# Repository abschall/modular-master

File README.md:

# modular-master

_Eurorack & Modular projects from Abschall_

Welcome to the Abschall Modular Repository !

Explore my published Eurorack modules:

[**REP**](/REP) - A two-channel 1-in-3 Audio Buffered Multiple.

[**ATOM**](/ATOM) - A versatile three-channel ATtenuverter, Offset, and Mixer, available in sleek 6HP and expanded 10HP versions.

[**2xVCA**](/2xVCA) - A dual VCA, based on the Mutable Instrument's Veils 2 design. 

[**MOUNTS**](/MOUNTS) - A dual ADSR module, whose circuit is based upon the famous Roland SH-101 ADSR.

These utility modules were crafted with care, serving my personal needs and now shared with the community. Stay tuned for forthcoming much more creative modules currently in development.

<br/><br/>
If you have any questions or want to make any comments, feel free to contact me on [Mod Wiggler](https://modwiggler.com/) or by email abschall@hotmail.com.

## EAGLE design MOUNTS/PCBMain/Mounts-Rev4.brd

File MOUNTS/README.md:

# MOUNTS - Dual ADSR

<div align="justify">
  
MOUNTS is a dual ADSR module. Each enveloppe is based on the Roland SH-101 ADSR, with some added feature. 

_Status:_

March 2024: Added Mounts to proto-branch.  
Mounts: Revision 4 (03/2024) is missing the panel design, which is in creation. 
Revision 4 has not been tested yet and is still a prototype/ The circuit is an improvement upon the 2021 Rev3 version. 

</div>

_License:_  

This work is licensed under [CC BY-SA 4.0]. (https://creativecommons.org/licenses/by-sa/4.0/)

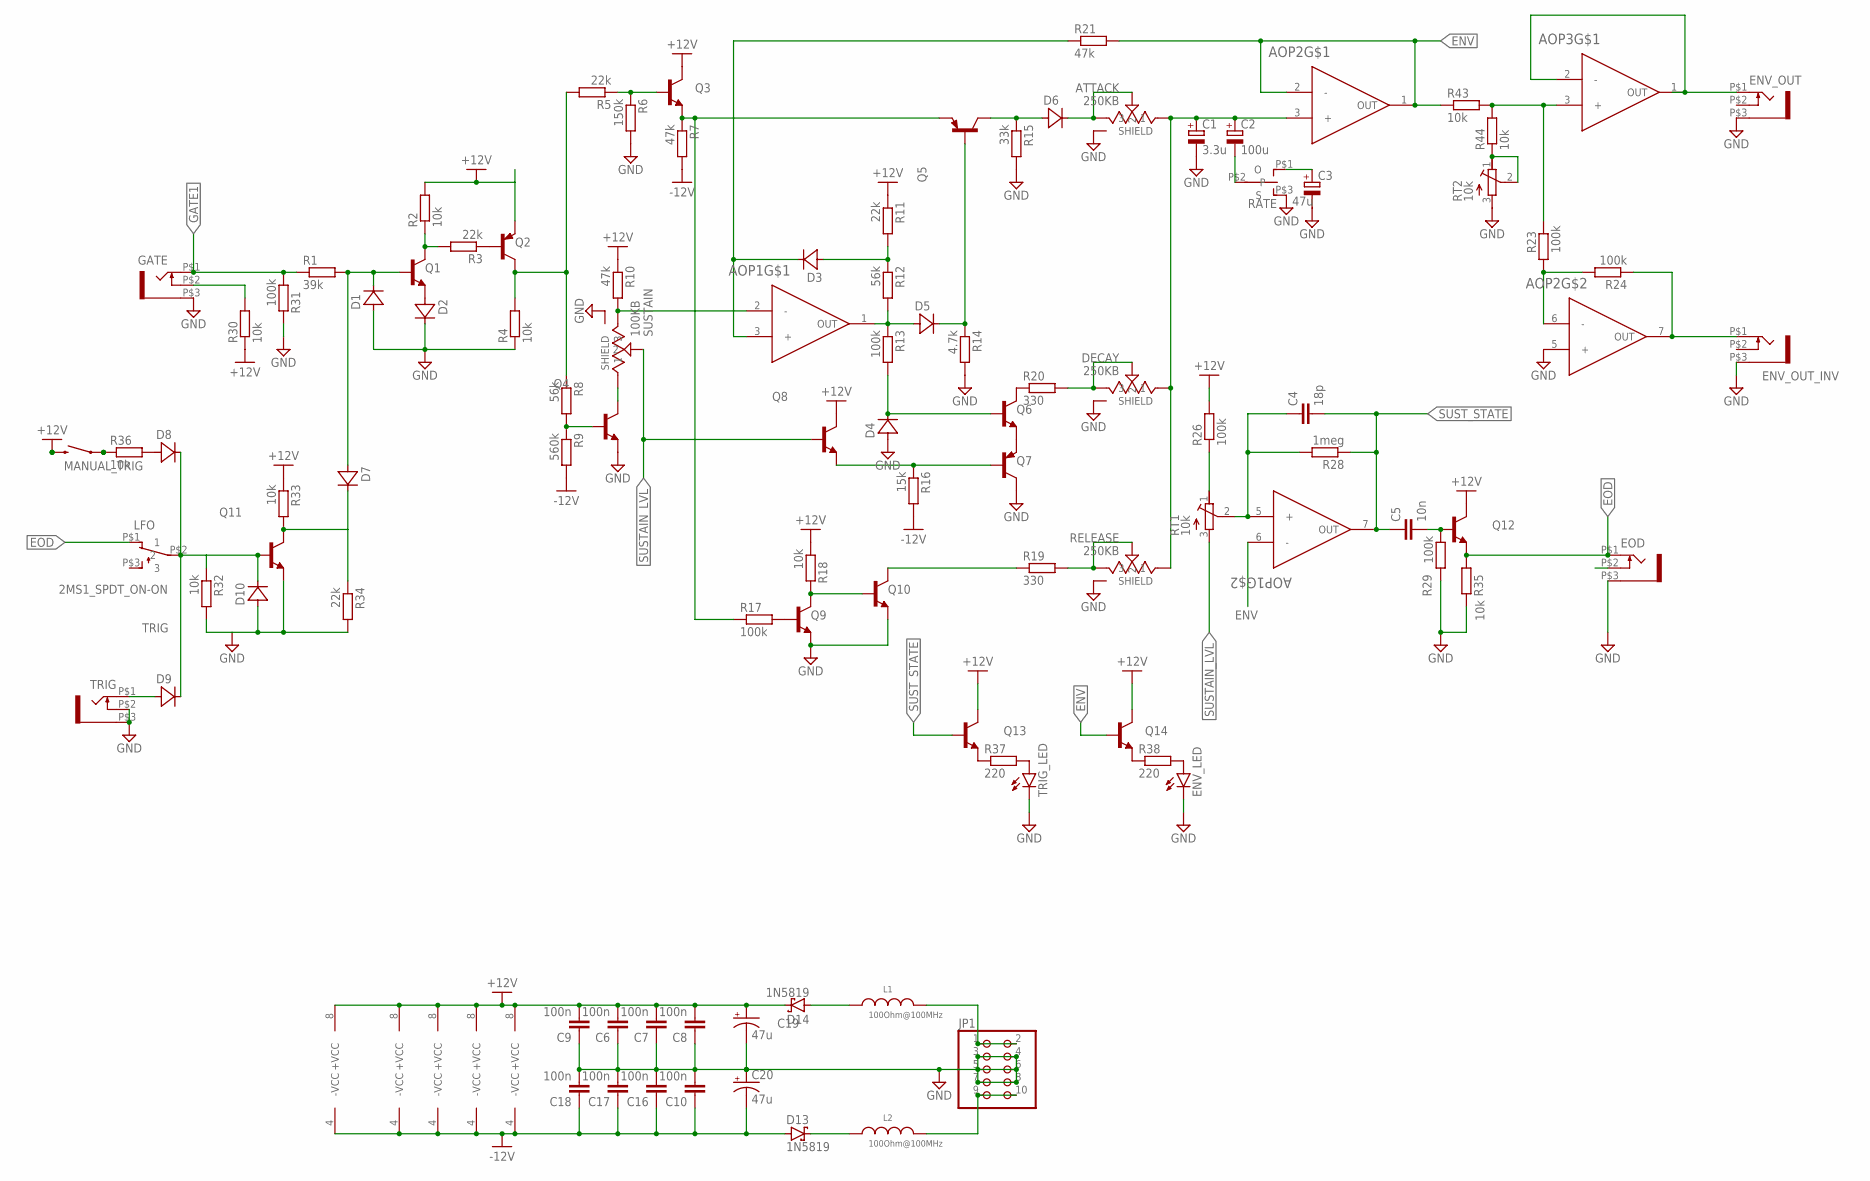
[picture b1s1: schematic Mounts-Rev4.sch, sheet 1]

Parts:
AOP1, AOP2, AOP3, AOP5, AOP6: TL072ACDR; SOIC8
ATTACK: 250KB; TRIM_PTA2043-2015CPB
C1: 3.3u; 153CLV-0405
C2: 100u; 153CLV-0605
C3: 47u; 153CLV-0605
C4: 18p; C0603
C5: 10n; C0603
C6, C7, C8, C9, C10, C16, C17, C18: 100n; C0603
C19, C20: 47u; PANASONIC_C
D1, D2, D3, D4, D5, D6, D7, D8, D9, D10: 1N4148WX; SOD323-W
D13, D14: 1N5819; SOD123
DECAY: 250KB; TRIM_PTA2043-2015CPB
ENV_LED: LED3MM
ENV_OUT: WQP-PJ301M-12_JACK
ENV_OUT_INV: WQP-PJ301M-12_JACK
EOD: WQP-PJ301M-12_JACK
GATE: WQP-PJ301M-12_JACK
JP1: PINHD-2X5; 2X05
L1, L2: 100Ohm@100MHz; WE-CBA_0603(W=2.2)
LFO: 2MS1_SPDT_ON-ON; 5FS1_SPDT
MANUAL_TRIG: MOMENTARY-SWITCH-SPST-PTH-6.0MM; TACTILE_SWITCH_PTH_6.0MM
Q1, Q3, Q4, Q6, Q8, Q9, Q10, Q11, Q12, Q13, Q14: MMBT3904; SOT23
Q2, Q5, Q7: MMBT3906; SOT23
R1: 39k; R0603
R2, R4, R18, R30, R32, R33, R35, R36, R43, R44: 10k; R0603
R3, R5, R11, R34: 22k; R0603
R6: 150k; R0603
R7, R10, R21: 47k; R0603
R8, R12: 56k; R0603
R9: 560k; R0603
R13, R17, R23, R24, R26, R29, R31: 100k; R0603
R14: 4.7k; R0603
R15: 33k; R0603
R16: 15k; R0603
R19, R20: 330; R0603
R28: 1meg; R0603
R37, R38: 220; R0603
RATE: 5FS1_SPDT_ON-OFF-ON; 5FS1_SPDT
RELEASE: 250KB; TRIM_PTA2043-2015CPB
RT1, RT2: 10k; RTRIM3314G
SUSTAIN: 100KB; TRIM_PTA2043-2015CPB
TRIG: WQP-PJ301M-12_JACK
TRIG_LED: LED3MM

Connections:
ENV: AOP1.6 (-), AOP2.1 (OUT), AOP2.2 (-), Q14.1 (B), R21.2, R43.1
EOD: EOD.P$1 (2), LFO.P$1 (1), Q12.2 (E), R35.1
GATE1: GATE.P$1 (2), R1.1, R31.1; also elsewhere on the board
GND: AOP2.5 (+), ATTACK.P1 (SHIELD), ATTACK.P2 (SHIELD), ATTACK.P3 (SHIELD), ATTACK.P4 (SHIELD), C1.-, C3.-, C6.1, C7.1, C8.1, C9.1, C10.2, C16.2, C17.2, C18.2, C19.-, C20.+, D1.A, D2.C, D4.A, D10.A, DECAY.P1 (SHIELD), DECAY.P2 (SHIELD), DECAY.P3 (SHIELD), DECAY.P4 (SHIELD), ENV_LED.K (C), ENV_OUT.P$3 (1), ENV_OUT_INV.P$3 (1), EOD.P$3 (1), GATE.P$3 (1), JP1.3, JP1.4, JP1.5, JP1.6, JP1.7, JP1.8, Q4.2 (E), Q7.3 (C), Q9.2 (E), Q10.2 (E), Q11.2 (E), R4.1, R6.2, R14.2, R15.2, R29.2, R31.2, R32.2, R34.2, R35.2, RATE.P$3 (S), RELEASE.P1 (SHIELD), RELEASE.P2 (SHIELD), RELEASE.P3 (SHIELD), RELEASE.P4 (SHIELD), RT2.3 (A), SUSTAIN.P1 (SHIELD), SUSTAIN.P2 (SHIELD), SUSTAIN.P3 (SHIELD), SUSTAIN.P4 (SHIELD), TRIG.P$2 (3), TRIG.P$3 (1), TRIG_LED.K (C); also elsewhere on the board
unnamed: D2.A, Q1.2 (E)
unnamed: D1.C, D7.A, Q1.1 (B), R1.2
unnamed: Q3.1 (B), R5.1, R6.1
unnamed: Q2.1 (B), R3.1
unnamed: JP1.1, JP1.2, L1.2
unnamed: Q1.3 (C), R2.1, R3.2
unnamed: AOP1.3 (+), D3.C, R21.1
unnamed: Q3.2 (E), Q5.2 (E), R7.1, R17.1
unnamed: Q4.1 (B), R8.2, R9.1
unnamed: AOP1.5 (+), C4.1, R28.2, RT1.2 (S)
unnamed: Q6.2 (E), Q7.2 (E)
unnamed: D3.A, R11.2, R12.1
unnamed: AOP1.1 (OUT), D5.A, R12.2, R13.1
unnamed: D4.C, Q6.1 (B), R13.2
unnamed: D5.C, Q5.1 (B), R14.1
unnamed: D6.A, Q5.3 (C), R15.1
unnamed: ATTACK.2, ATTACK.3, D6.C
unnamed: Q7.1 (B), Q8.2 (E), R16.1
unnamed: Q9.1 (B), R17.2
unnamed: AOP1.2 (-), R10.2, SUSTAIN.3
unnamed: Q9.3 (C), Q10.1 (B), R18.2
unnamed: Q10.3 (C), R19.1
unnamed: Q6.3 (C), R20.1
unnamed: DECAY.2, DECAY.3, R20.2
unnamed: R19.2, RELEASE.2, RELEASE.3
unnamed: AOP2.3 (+), ATTACK.1, C1.+, C2.+, DECAY.1, RELEASE.1
unnamed: Q4.3 (C), SUSTAIN.1
unnamed: AOP2.6 (-), R23.1, R24.2
unnamed: AOP3.1 (OUT), AOP3.2 (-), ENV_OUT.P$1 (2)
unnamed: GATE.P$2 (3), R30.2
unnamed: Q2.3 (C), R4.2, R5.2, R8.1
unnamed: R26.1, RT1.1 (E)
unnamed: D8.A, R36.2
unnamed: R44.1, RT2.1 (E), RT2.2 (S)
unnamed: D9.A, TRIG.P$1 (2)
unnamed: D7.C, Q11.3 (C), R33.2, R34.1
unnamed: C5.2, Q12.1 (B), R29.1
unnamed: MANUAL_TRIG.3 (2), R36.1
unnamed: C2.-, RATE.P$2
unnamed: C3.+, RATE.P$1 (O)
unnamed: Q13.2 (E), R37.1
unnamed: R37.2, TRIG_LED.A
unnamed: Q14.2 (E), R38.1
unnamed: ENV_LED.A, R38.2
unnamed: AOP2.7 (OUT), ENV_OUT_INV.P$1 (2), R24.1
unnamed: AOP3.3 (+), R23.2, R43.2, R44.2
unnamed: JP1.9, JP1.10, L2.2
unnamed: D14.A, L1.1
unnamed: D13.C, L2.1
SUSTAIN_LVL: Q8.1 (B), RT1.3 (A), SUSTAIN.2
SUST_STATE: AOP1.7 (OUT), C4.2, C5.1, Q13.1 (B), R28.1
TRIG: D8.C, D9.C, D10.C, LFO.P$2 (2), Q11.1 (B), R32.1
VCC: AOP1.8 (+VCC), AOP2.8 (+VCC), AOP3.8 (+VCC), AOP5.8 (+VCC), AOP6.8 (+VCC), C6.2, C7.2, C8.2, C9.2, C19.+, D14.C, MANUAL_TRIG.1, Q2.2 (E), Q3.3 (C), Q8.3 (C), Q12.3 (C), Q13.3 (C), Q14.3 (C), R2.2, R10.1, R11.1, R18.1, R26.2, R30.1, R33.1; also elsewhere on the board
VDD: AOP1.4 (-VCC), AOP2.4 (-VCC), AOP3.4 (-VCC), AOP5.4 (-VCC), AOP6.4 (-VCC), C10.1, C16.1, C17.1, C18.1, C20.-, D13.A, R7.2, R9.2, R16.2; also elsewhere on the board

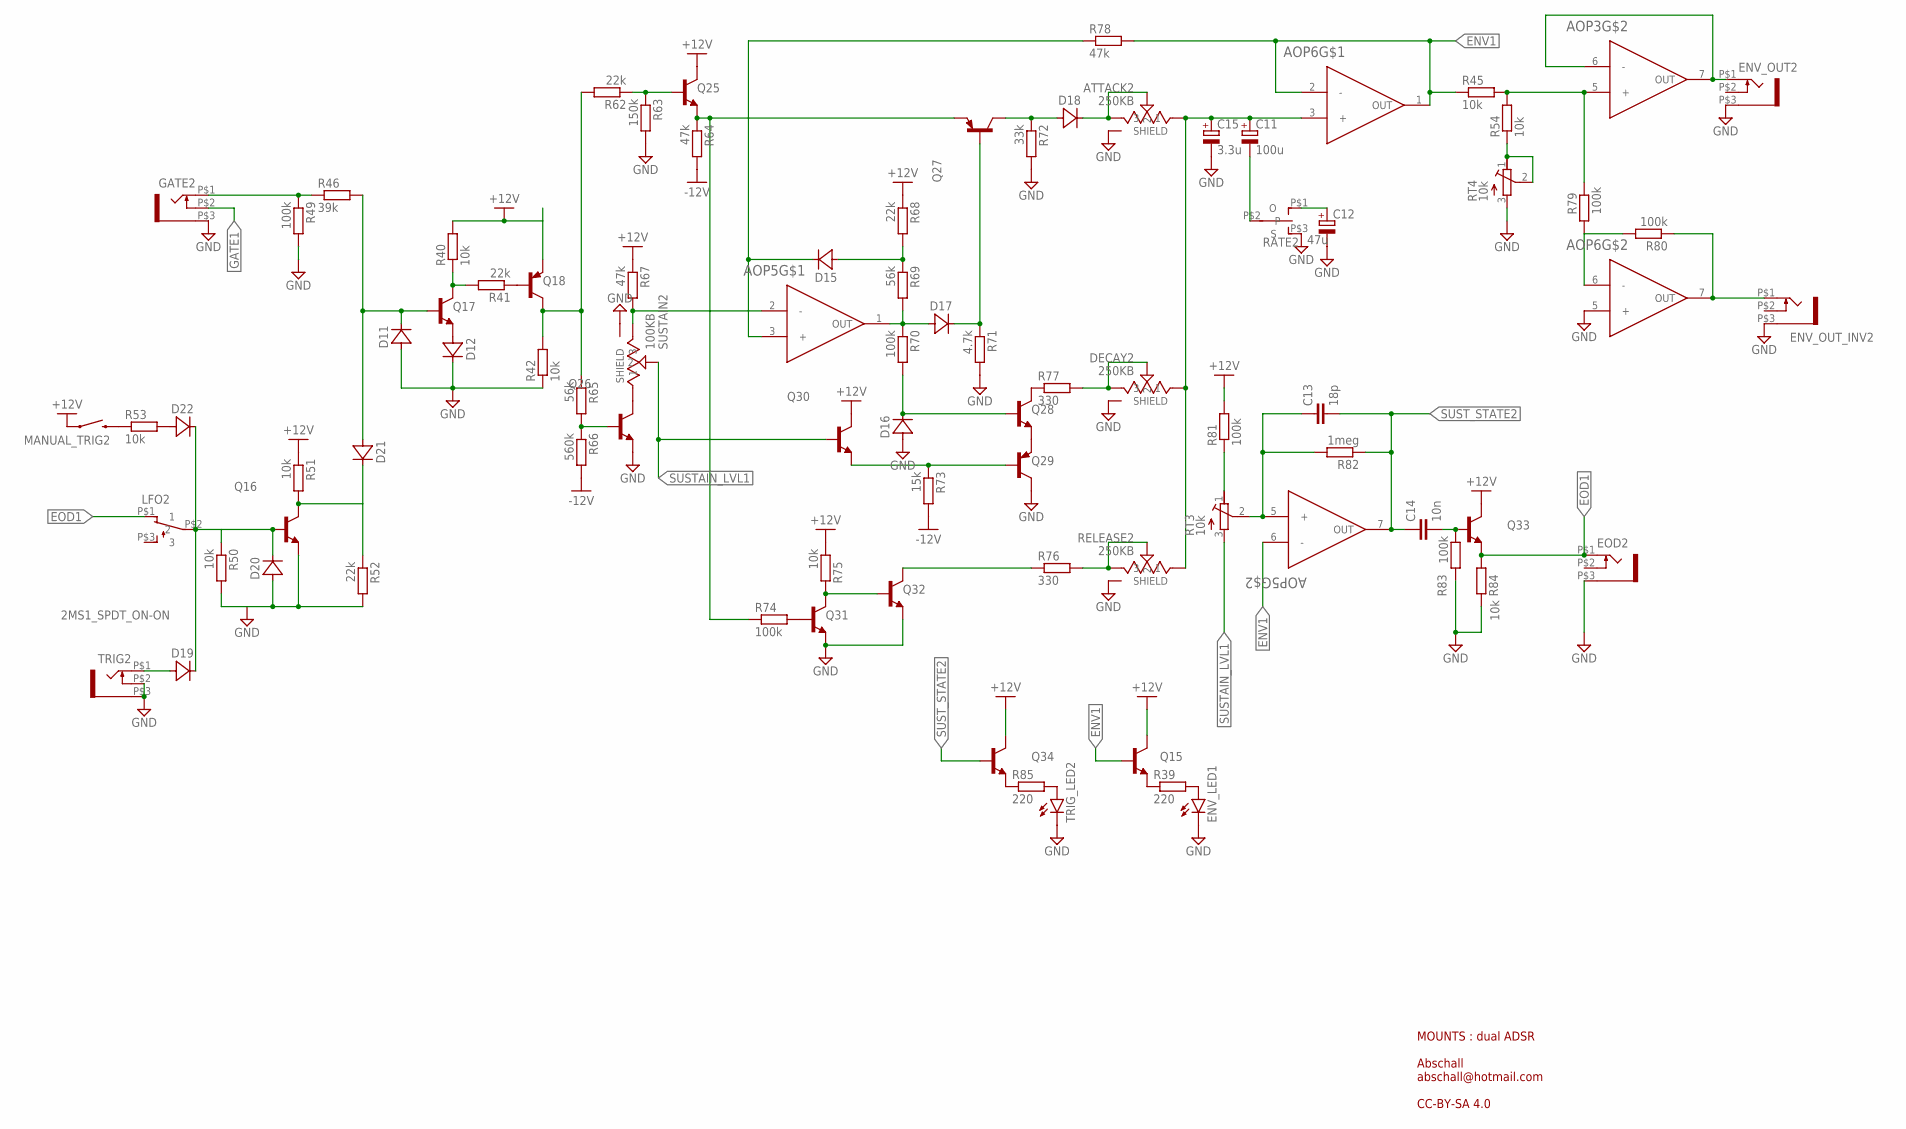
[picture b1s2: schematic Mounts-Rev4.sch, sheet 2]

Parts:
AOP3, AOP5, AOP6: TL072ACDR; SOIC8
ATTACK2: 250KB; TRIM_PTA2043-2015CPB
C11: 100u; 153CLV-0605
C12: 47u; 153CLV-0605
C13: 18p; C0603
C14: 10n; C0603
C15: 3.3u; 153CLV-0405
D11, D12, D15, D16, D17, D18, D19, D20, D21, D22: 1N4148WX; SOD323-W
DECAY2: 250KB; TRIM_PTA2043-2015CPB
ENV_LED1: LED3MM
ENV_OUT2: WQP-PJ301M-12_JACK
ENV_OUT_INV2: WQP-PJ301M-12_JACK
EOD2: WQP-PJ301M-12_JACK
GATE2: WQP-PJ301M-12_JACK
LFO2: 2MS1_SPDT_ON-ON; 5FS1_SPDT
MANUAL_TRIG2: MOMENTARY-SWITCH-SPST-PTH-6.0MM; TACTILE_SWITCH_PTH_6.0MM
Q15, Q16, Q17, Q25, Q26, Q28, Q30, Q31, Q32, Q33, Q34: MMBT3904; SOT23
Q18, Q27, Q29: MMBT3906; SOT23
R39, R85: 220; R0603
R40, R42, R45, R50, R51, R53, R54, R75, R84: 10k; R0603
R41, R52, R62, R68: 22k; R0603
R46: 39k; R0603
R49, R70, R74, R79, R80, R81, R83: 100k; R0603
R63: 150k; R0603
R64, R67, R78: 47k; R0603
R65, R69: 56k; R0603
R66: 560k; R0603
R71: 4.7k; R0603
R72: 33k; R0603
R73: 15k; R0603
R76, R77: 330; R0603
R82: 1meg; R0603
RATE2: 5FS1_SPDT_ON-OFF-ON; 5FS1_SPDT
RELEASE2: 250KB; TRIM_PTA2043-2015CPB
RT3, RT4: 10k; RTRIM3314G
SUSTAIN2: 100KB; TRIM_PTA2043-2015CPB
TRIG2: WQP-PJ301M-12_JACK
TRIG_LED2: LED3MM

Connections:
ENV1: AOP5.6 (-), AOP6.1 (OUT), AOP6.2 (-), Q15.1 (B), R45.1, R78.2
EOD1: EOD2.P$1 (2), LFO2.P$1 (1), Q33.2 (E), R84.1
GATE1: GATE2.P$2 (3); also elsewhere on the board
GND: AOP6.5 (+), ATTACK2.P1 (SHIELD), ATTACK2.P2 (SHIELD), ATTACK2.P3 (SHIELD), ATTACK2.P4 (SHIELD), C12.-, C15.-, D11.A, D12.C, D16.A, D20.A, DECAY2.P1 (SHIELD), DECAY2.P2 (SHIELD), DECAY2.P3 (SHIELD), DECAY2.P4 (SHIELD), ENV_LED1.K (C), ENV_OUT2.P$3 (1), ENV_OUT_INV2.P$3 (1), EOD2.P$3 (1), GATE2.P$3 (1), Q16.2 (E), Q26.2 (E), Q29.3 (C), Q31.2 (E), Q32.2 (E), R42.1, R49.2, R50.2, R52.2, R63.2, R71.2, R72.2, R83.2, R84.2, RATE2.P$3 (S), RELEASE2.P1 (SHIELD), RELEASE2.P2 (SHIELD), RELEASE2.P3 (SHIELD), RELEASE2.P4 (SHIELD), RT4.3 (A), SUSTAIN2.P1 (SHIELD), SUSTAIN2.P2 (SHIELD), SUSTAIN2.P3 (SHIELD), SUSTAIN2.P4 (SHIELD), TRIG2.P$2 (3), TRIG2.P$3 (1), TRIG_LED2.K (C); also elsewhere on the board
unnamed: AOP6.6 (-), R79.1, R80.2
unnamed: AOP3.5 (+), R45.2, R54.2, R79.2
unnamed: D12.A, Q17.2 (E)
unnamed: Q15.2 (E), R39.1
unnamed: ENV_LED1.A, R39.2
unnamed: D11.C, D21.A, Q17.1 (B), R46.2
unnamed: Q18.1 (B), R41.1
unnamed: Q17.3 (C), R40.1, R41.2
unnamed: Q18.3 (C), R42.2, R62.2, R65.1
unnamed: GATE2.P$1 (2), R46.1, R49.1
unnamed: R54.1, RT4.1 (E), RT4.2 (S)
unnamed: D21.C, Q16.3 (C), R51.2, R52.1
unnamed: D19.A, TRIG2.P$1 (2)
unnamed: D22.A, R53.2
unnamed: MANUAL_TRIG2.3 (2), R53.1
unnamed: AOP3.6 (-), AOP3.7 (OUT), ENV_OUT2.P$1 (2)
unnamed: AOP5.2 (-), R67.2, SUSTAIN2.3
unnamed: Q26.3 (C), SUSTAIN2.1
unnamed: Q25.1 (B), R62.1, R63.1
unnamed: Q25.2 (E), Q27.2 (E), R64.1, R74.1
unnamed: Q26.1 (B), R65.2, R66.1
unnamed: AOP5.3 (+), D15.C, R78.1
unnamed: D15.A, R68.2, R69.1
unnamed: AOP5.1 (OUT), D17.A, R69.2, R70.1
unnamed: D16.C, Q28.1 (B), R70.2
unnamed: D17.C, Q27.1 (B), R71.1
unnamed: D18.A, Q27.3 (C), R72.1
unnamed: ATTACK2.2, ATTACK2.3, D18.C
unnamed: Q28.2 (E), Q29.2 (E)
unnamed: Q29.1 (B), Q30.2 (E), R73.1
unnamed: Q31.1 (B), R74.2
unnamed: Q31.3 (C), Q32.1 (B), R75.2
unnamed: Q32.3 (C), R76.1
unnamed: Q28.3 (C), R77.1
unnamed: DECAY2.2, DECAY2.3, R77.2
unnamed: R76.2, RELEASE2.2, RELEASE2.3
unnamed: AOP6.3 (+), ATTACK2.1, C11.+, C15.+, DECAY2.1, RELEASE2.1
unnamed: AOP6.7 (OUT), ENV_OUT_INV2.P$1 (2), R80.1
unnamed: R81.1, RT3.1 (E)
unnamed: AOP5.5 (+), C13.1, R82.2, RT3.2 (S)
unnamed: C14.2, Q33.1 (B), R83.1
unnamed: C11.-, RATE2.P$2
unnamed: C12.+, RATE2.P$1 (O)
unnamed: Q34.2 (E), R85.1
unnamed: R85.2, TRIG_LED2.A
SUSTAIN_LVL1: Q30.1 (B), RT3.3 (A), SUSTAIN2.2
SUST_STATE2: AOP5.7 (OUT), C13.2, C14.1, Q34.1 (B), R82.1
TRIG1: D19.C, D20.C, D22.C, LFO2.P$2 (2), Q16.1 (B), R50.1
VCC: MANUAL_TRIG2.1, Q15.3 (C), Q18.2 (E), Q25.3 (C), Q30.3 (C), Q33.3 (C), Q34.3 (C), R40.2, R51.1, R67.1, R68.1, R75.1, R81.2; also elsewhere on the board
VDD: R64.2, R66.2, R73.2; also elsewhere on the board

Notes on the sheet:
MOUNTS : dual ADSR Abschall abschall@hotmail.com CC-BY-SA 4.0

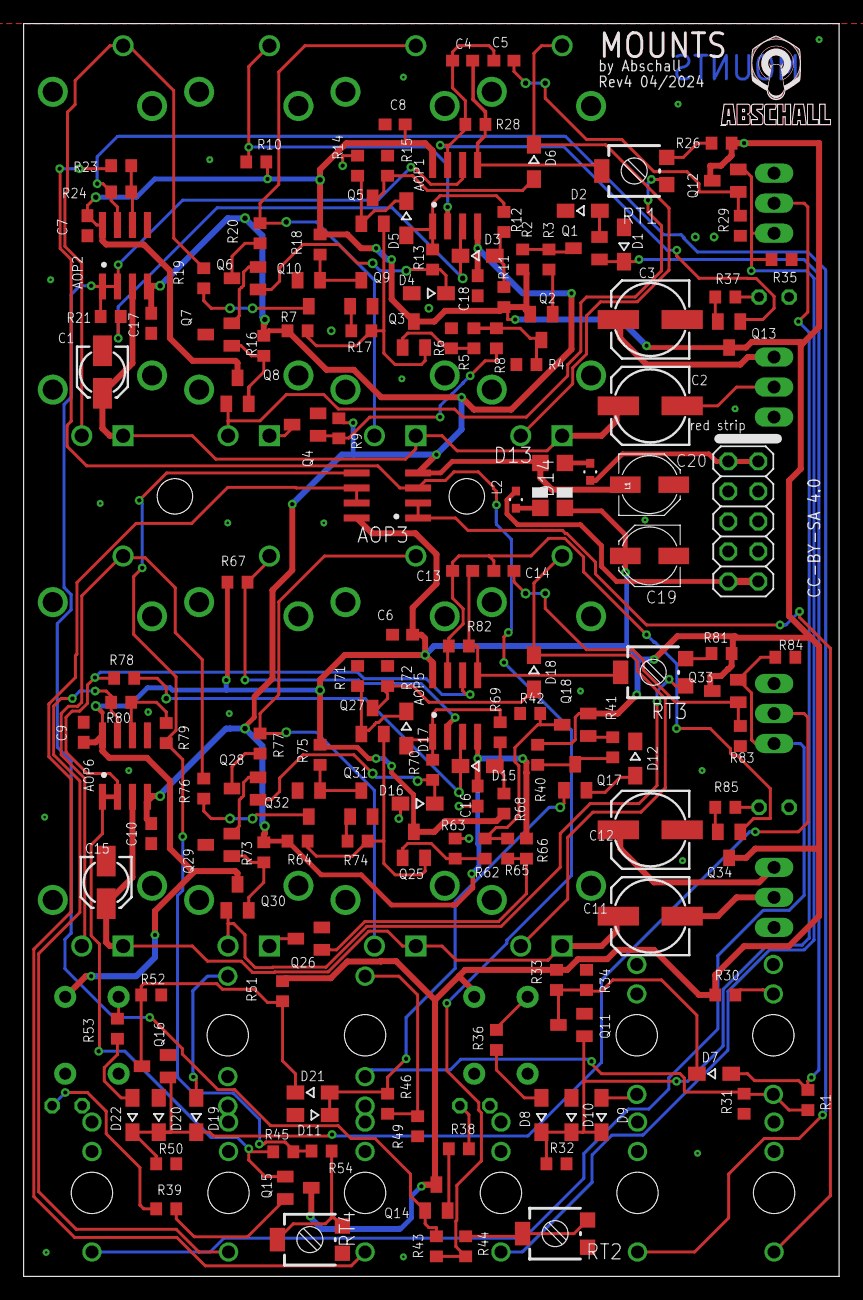
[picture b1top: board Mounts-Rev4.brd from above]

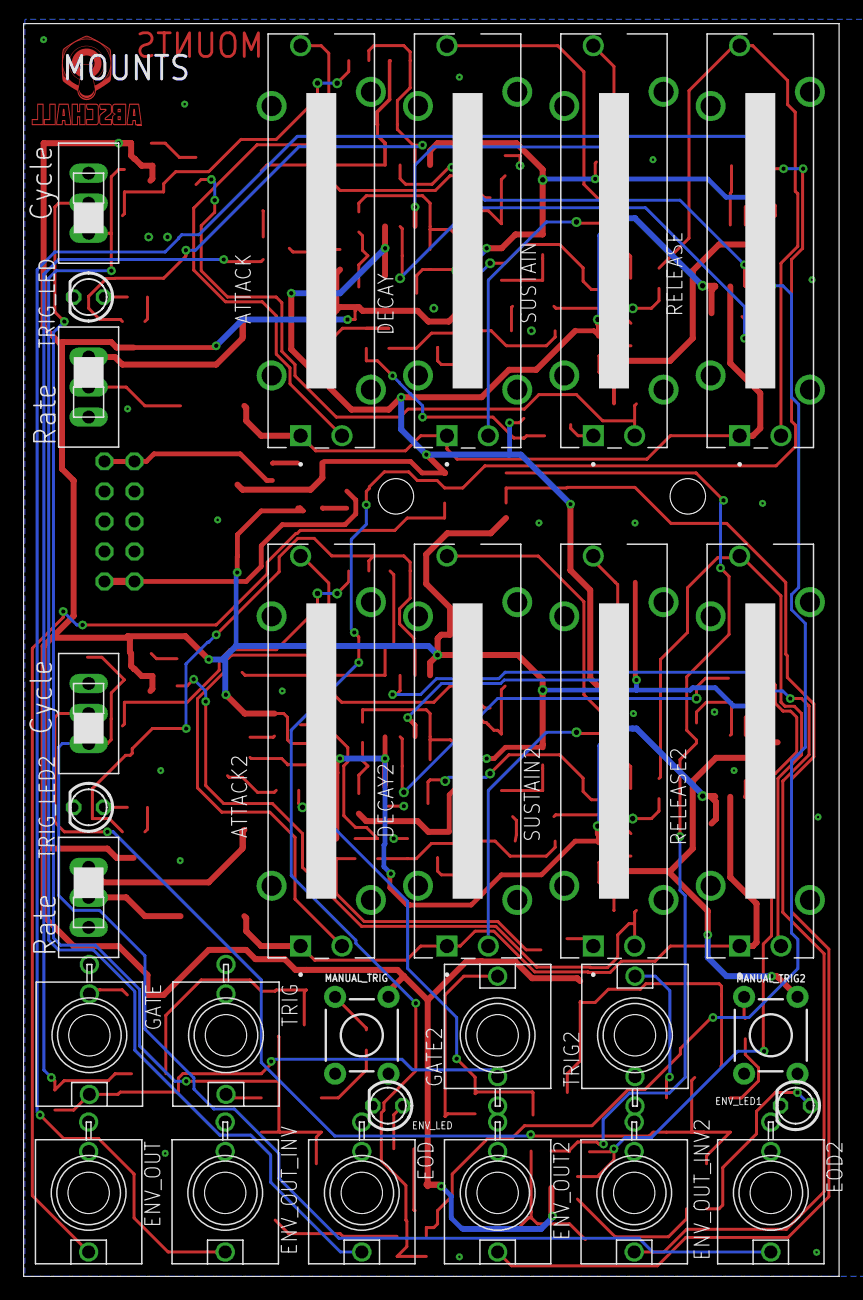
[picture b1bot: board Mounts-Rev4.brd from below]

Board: 2 copper layers, 69.0 x 106.0 mm, 183 parts (28 on the bottom side), 108 nets.

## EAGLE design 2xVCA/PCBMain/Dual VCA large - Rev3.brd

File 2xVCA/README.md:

# 2x VCA - Dual Voltage-Controlled Amplifier

<div align="justify">
  
2x VCA is a two-channel VCA based on Mutable Instruments' Veils, designed by Émilie Gillet. It features two separate voltage-controlled amplifiers, each with gain and response curve potentiometers, which are variable from linear to exponential. The PCB has been adapted to create a larger, more performance-friendly module for my purposes, providing more space between the jacks and knobs.

The module is 8HP wide and 21mm deep.

The PCB utilizes 0805 format surface-mount device (SMD) components.

</div>

_Status:_

March 2024: Publication of the project.  
2xVCA: Revision 3 (03/2022)  

_License:_  

This work is licensed under [CC BY-SA 3.0]. Circuit by Émilie GILLET, adaptation by Abschall. (https://creativecommons.org/licenses/by-sa/3.0/)

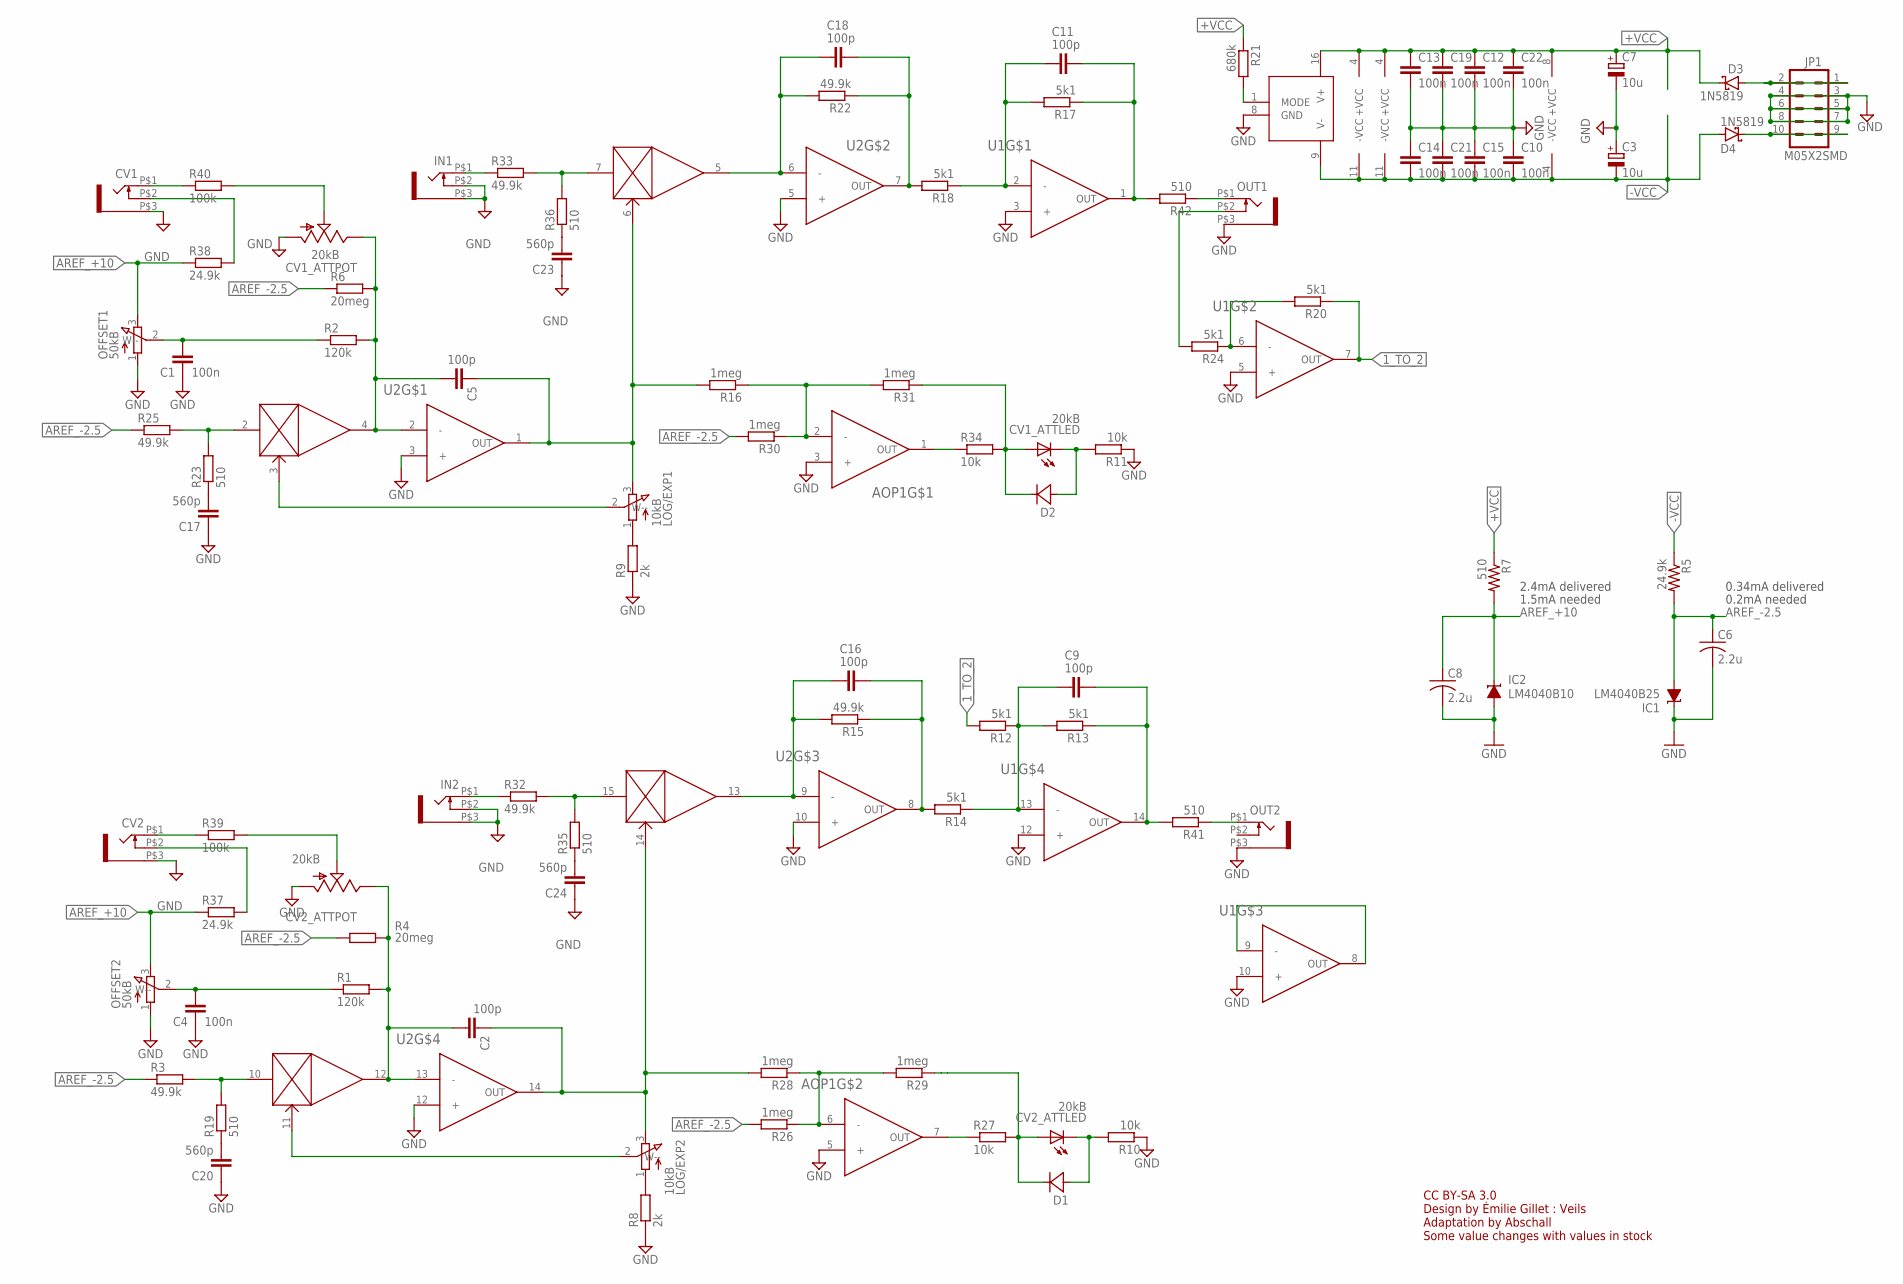
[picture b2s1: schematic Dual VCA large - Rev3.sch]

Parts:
AOP1: TL072ACDR; SOIC8
C1, C4, C10, C12, C13, C14, C15, C19, C21, C22: 100n; C0805K
C2, C5, C9, C11, C16, C18: 100p; C0805K
C3, C7: 10u; PANASONIC_B
C6, C8: 2.2u; C0805
C17, C20, C23, C24: 560p; C0805K
CV1, CV2: WQP-PJ301M-12_JACK
CV1_ATT, CV2_ATT: 20kB; BOURNS_SLIDER
D1, D2: 1N4148WX; SOD323-W
D3, D4: 1N5819; SOD123
IC1: LM4040B25; DBZ_R-PDSO-G3
IC2: LM4040B10; DBZ_R-PDSO-G3
IN1, IN2: WQP-PJ301M-12_JACK
JP1: M05X2SMD; 2X5-SMD
LOG/EXP1, LOG/EXP2: 10kB; ALPHA9MM-SH
OFFSET1, OFFSET2: 50kB; ALPHA9MM-SH
OUT1, OUT2: WQP-PJ301M-12_JACK
R1, R2: 120k; R0805
R3, R15, R22, R25, R32, R33: 49.9k; R0805
R4, R6: 20meg; R0805
R5, R37, R38: 24.9k; R0805
R7, R19, R23, R35, R36, R41, R42: 510; R0805
R8, R9: 2k; R0805
R10, R11, R27, R34: 10k; R0805
R12, R13, R14, R17, R18, R20, R24: 5k1; R0805
R16, R26, R28, R29, R30, R31: 1meg; R0805
R21: 680k; R0805
R39, R40: 100k; R0805
U1, U2: TL74CD; SO14
VCA1: V2164SOIC16N; SOIC16N

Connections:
1_TO_2: R12.2, R20.1, U1.7 (OUT)
+VCC: AOP1.8 (+VCC), C7.+, C12.1, C13.1, C19.1, C22.1, D3.C, R7.1, R21.1, U1.4 (+VCC), U2.4 (+VCC), VCA1.16 (V+)
-VCC: AOP1.4 (-VCC), C3.-, C10.2, C14.2, C15.2, C21.2, D4.A, R5.1, U1.11 (-VCC), U2.11 (-VCC), VCA1.9 (V-)
AREF_+10: C8.1, IC2.1 (C), OFFSET1.3, OFFSET2.3, R7.2, R37.1, R38.1
AREF_-2.5: C6.1, IC1.2 (A), R3.1, R4.1, R5.2, R6.1, R25.1, R26.2, R30.2
GND: AOP1.3 (+), AOP1.5 (+), C1.1, C3.+, C4.1, C6.2, C7.-, C8.2, C10.1, C12.2, C13.2, C14.1, C15.1, C17.1, C19.2, C20.1, C21.1, C22.2, C23.1, C24.1, CV1.P$3 (1), CV1_ATT.1 (A), CV2.P$3 (1), CV2_ATT.1 (A), IC1.1 (C), IC2.2 (A), IN1.P$2 (3), IN1.P$3 (1), IN2.P$2 (3), IN2.P$3 (1), JP1.3, JP1.4, JP1.5, JP1.6, JP1.7, JP1.8, OFFSET1.1, OFFSET2.1, OUT1.P$3 (1), OUT2.P$3 (1), R8.1, R9.1, R10.1, R11.1, U1.3 (+), U1.5 (+), U1.10 (+), U1.12 (+), U2.3 (+), U2.5 (+), U2.10 (+), U2.12 (+), VCA1.8 (GND)
unnamed: C23.2, R36.1
unnamed: CV2.P$1 (2), R39.1
unnamed: R33.2, R36.2, VCA1.7 (IN)
unnamed: C18.2, R22.2, U2.6 (-), VCA1.5 (OUT)
unnamed: C5.2, CV1_ATT.3 (E), R2.2, R6.2, U2.2 (-), VCA1.4 (OUT)
unnamed: IN2.P$1 (2), R32.1
unnamed: R21.2, VCA1.1 (MODE)
unnamed: C1.2, OFFSET1.2 (W--), R2.1
unnamed: C5.1, LOG/EXP1.3, R16.2, U2.1 (OUT), VCA1.6 (CV)
unnamed: C17.2, R23.1
unnamed: LOG/EXP1.1, R9.2
unnamed: R23.2, R25.2, VCA1.2 (IN)
unnamed: LOG/EXP1.2 (W--), VCA1.3 (CV)
unnamed: CV1_ATT.2 (S), R40.2
unnamed: C11.2, R17.2, R18.1, U1.2 (-)
unnamed: R20.2, R24.1, U1.6 (-)
unnamed: CV1_ATT.E (C), D2.A, R11.2
unnamed: CV2_ATT.B (A), D1.C, R27.2, R29.1
unnamed: IN1.P$1 (2), R33.1
unnamed: CV1.P$2 (3), R38.2
unnamed: OUT1.P$1 (2), R42.1
unnamed: OUT1.P$2 (3), R24.2
unnamed: C24.2, R35.1
unnamed: R32.2, R35.2, VCA1.15 (IN)
unnamed: C16.2, R15.2, U2.9 (-), VCA1.13 (OUT)
unnamed: C2.1, LOG/EXP2.3, R28.2, U2.14 (OUT), VCA1.14 (CV)
unnamed: C20.2, R19.1
unnamed: R3.2, R19.2, VCA1.10 (IN)
unnamed: LOG/EXP2.1, R8.2
unnamed: LOG/EXP2.2 (W--), VCA1.11 (CV)
unnamed: C2.2, CV2_ATT.3 (E), R1.2, R4.2, U2.13 (-), VCA1.12 (OUT)
unnamed: C4.2, OFFSET2.2 (W--), R1.1
unnamed: CV2_ATT.2 (S), R39.2
unnamed: C9.2, R12.1, R13.2, R14.1, U1.13 (-)
unnamed: U1.8 (OUT), U1.9 (-)
unnamed: CV1_ATT.B (A), D2.C, R31.1, R34.2
unnamed: CV1.P$1 (2), R40.1
unnamed: CV2.P$2 (3), R37.2
unnamed: OUT2.P$1 (2), R41.1
unnamed: D4.C, JP1.9, JP1.10
unnamed: AOP1.1 (OUT), R34.1
unnamed: AOP1.2 (-), R16.1, R30.1, R31.2
unnamed: CV2_ATT.E (C), D1.A, R10.2
unnamed: AOP1.7 (OUT), R27.1
unnamed: AOP1.6 (-), R26.1, R28.1, R29.2
unnamed: D3.A, JP1.1, JP1.2
OUT: C18.1, R18.2, R22.1, U2.7 (OUT)
OUT1: C11.1, R17.1, R42.2, U1.1 (OUT)
OUT2: C16.1, R14.2, R15.1, U2.8 (OUT)
OUT3: C9.1, R13.1, R41.2, U1.14 (OUT)

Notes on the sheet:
0.34mA delivered
2.4mA delivered
0.2mA needed
1.5mA needed
CC BY-SA 3.0 Design by Émilie Gillet : Veils Adaptation by Abschall Some value changes with values in stock

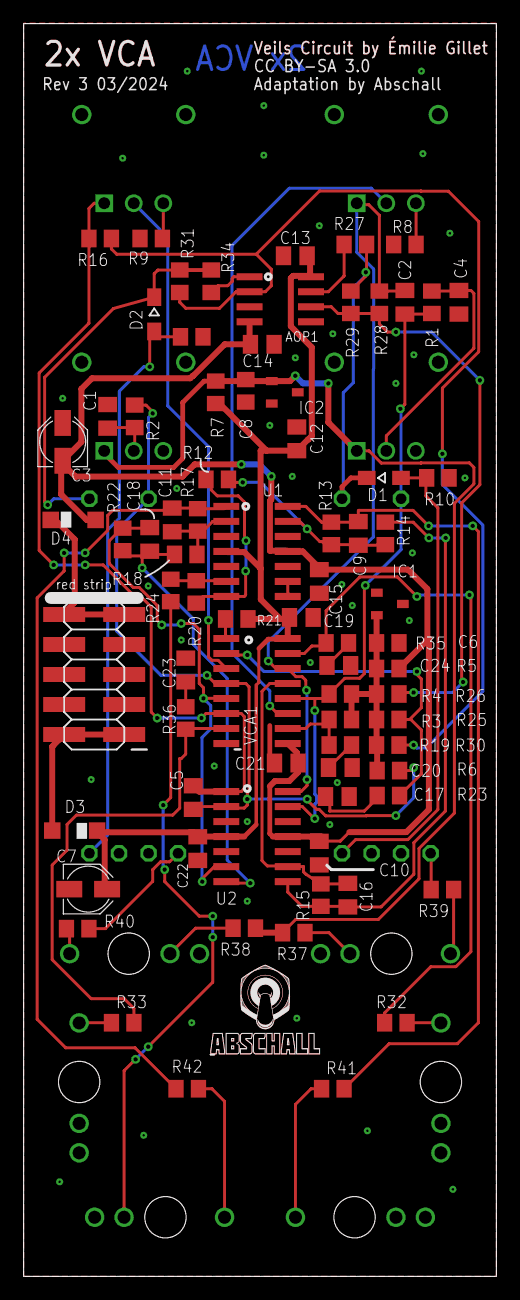
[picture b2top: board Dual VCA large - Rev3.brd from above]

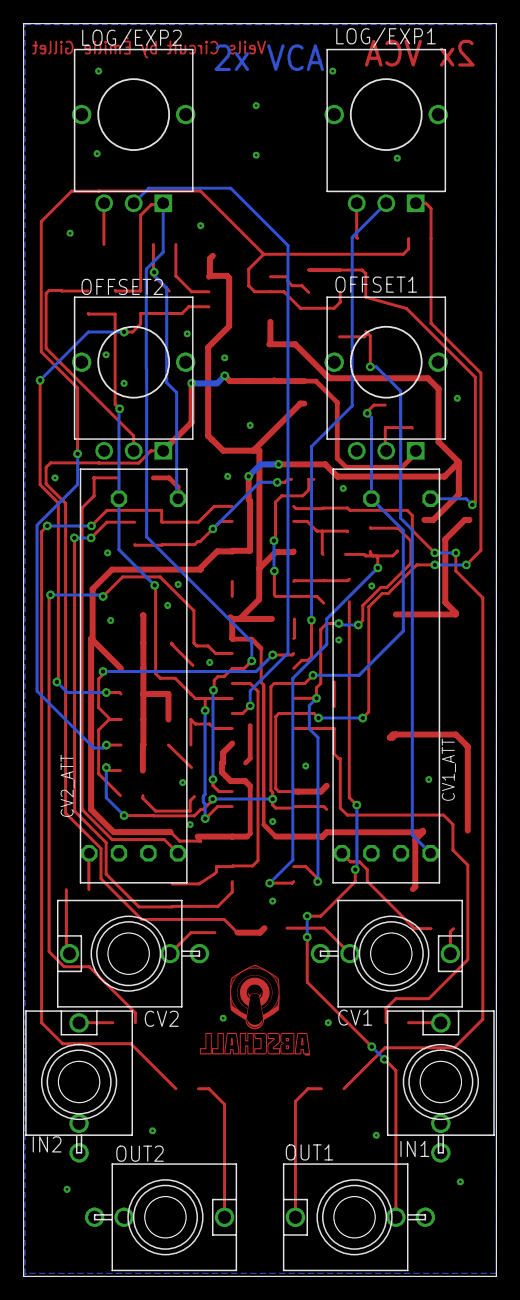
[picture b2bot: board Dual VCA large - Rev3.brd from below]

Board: 2 copper layers, 40.0 x 106.0 mm, 89 parts (12 on the bottom side), 56 nets.

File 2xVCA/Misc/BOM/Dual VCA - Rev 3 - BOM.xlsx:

Dual VCA - Rev 2 - BOM
Qty | Value | Device | Package | Parts | Description | Bought | Built
Resistors
7 | 510 | R-EU_R0805 | R0805 | R7, R19, R23, R35, R36, R41, R42 | RESISTOR, European symbol
2 | 2k | R-EU_R0805 | R0805 | R8, R9 | RESISTOR, European symbol
7 | 5k1 | R-EU_R0805 | R0805 | R12, R13, R14, R17, R18, R20, R24 | RESISTOR, European symbol
4 | 10k * | R-EU_R0805 | R0805 | R10, R11, R27, R34 | RESISTOR, European symbol
2 | 24.9k | R-EU_R0805 | R0805 | R37, R38 | RESISTOR, European symbol
6 | 49.9k | R-EU_R0805 | R0805 | R3, R15, R22, R25, R32, R33 | RESISTOR, European symbol
2 | 100k | R-EU_R0805 | R0805 | R39, R40 | RESISTOR, European symbol
2 | 120k | R-EU_R0805 | R0805 | R1, R2 | RESISTOR, European symbol
1 | 680k | R-EU_R0805 | R0805 | R21 | RESISTOR, European symbol
6 | 1meg | R-EU_R0805 | R0805 | R16, R26, R28, R29, R30, R31 | RESISTOR, European symbol
2 | 20meg | R-EU_R0805 | R0805 | R4, R6 | RESISTOR, European symbol
Capacitors
6 | 100p | C-EUC0805K | C0805K | C2, C5, C9, C11, C16, C18 | CAPACITOR, European symbol
4 | 560p | C-EUC0805K | C0805K | C17, C20, C23, C24 | CAPACITOR, European symbol
10 | 100n | C-EUC0805K | C0805K | C1, C4, C10, C12, C13, C14, C15, C19, C21, C22 | CAPACITOR, European symbol
2 | 2.2u | C-USC0805 | C0805 | C6, C8 | CAPACITOR, American symbol
2 | 10u | CPOL-EUB | PANASONIC_B | C3, C7 | POLARIZED CAPACITOR, European symbol
Ics
2 | 1N5819 | 1N5819 | SOD123 | D3, D4 | Schottky Diode
2 |  | 1N4148WX | SOD323-W | D1, D2 | Regular Diode
1 |  | TL072ACDR | SOIC8 | AOP1 | Dual Op-Amp
2 |  | TL74CD | SO14 | U1, U2 | Quad Op-Amp
1 |  | LM4041B12DBZ | DBZ_R-PDSO-G3 | IC2 | PRECISION MICROPOWER SHUNT VOLTAGE REFERENCE
1 | LM4040B25 | LM4041B12DBZ | DBZ_R-PDSO-G3 | IC1 | PRECISION MICROPOWER SHUNT VOLTAGE REFERENCE
1 | V2164SOIC16N | V2164SOIC16N | SOIC16N | VCA1 | 2164 Quad VCA chip
Through Hole Stuff
2 | 20kB | BOURNS_SLIDER | BOURNS_SLIDER | CV1_ATT, CV2_ATT
2 | 10kB | ALPHA9MMSMALL_HOLE | ALPHA9MM-SH | LOG/EXP1, LOG/EXP2
2 | 50kB | ALPHA9MMSMALL_HOLE | ALPHA9MM-SH | OFFSET1, OFFSET2
1 | M05X2SMD | M05X2SMD | 2X5-SMD | JP1 | Header 5x2
6 | PJ301M |  |  | CV1, CV2, IN1, IN2, OUT1, OUT2 | Thonkiconn
 | * | 24.9k in original Veils

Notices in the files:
parts and their libraries:
SparkFun-Switches: Licensing: Creative Commons ShareAlike 4.0 International - https://creativecommons.org/licenses/by-sa/4.0
Wurth_Automotive_WE-CBA: Copyright: Würth Elektronik
